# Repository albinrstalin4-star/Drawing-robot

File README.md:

# Drawing-robot
I want to create a drawing robot for my assignments. I think it will be helpful.This is my first project.This project is about building a simple drawing plotter robot that can automatically draw pictures and text on paper. It uses NEMA stepper motors to move a pen precisely along the X and Y directions.

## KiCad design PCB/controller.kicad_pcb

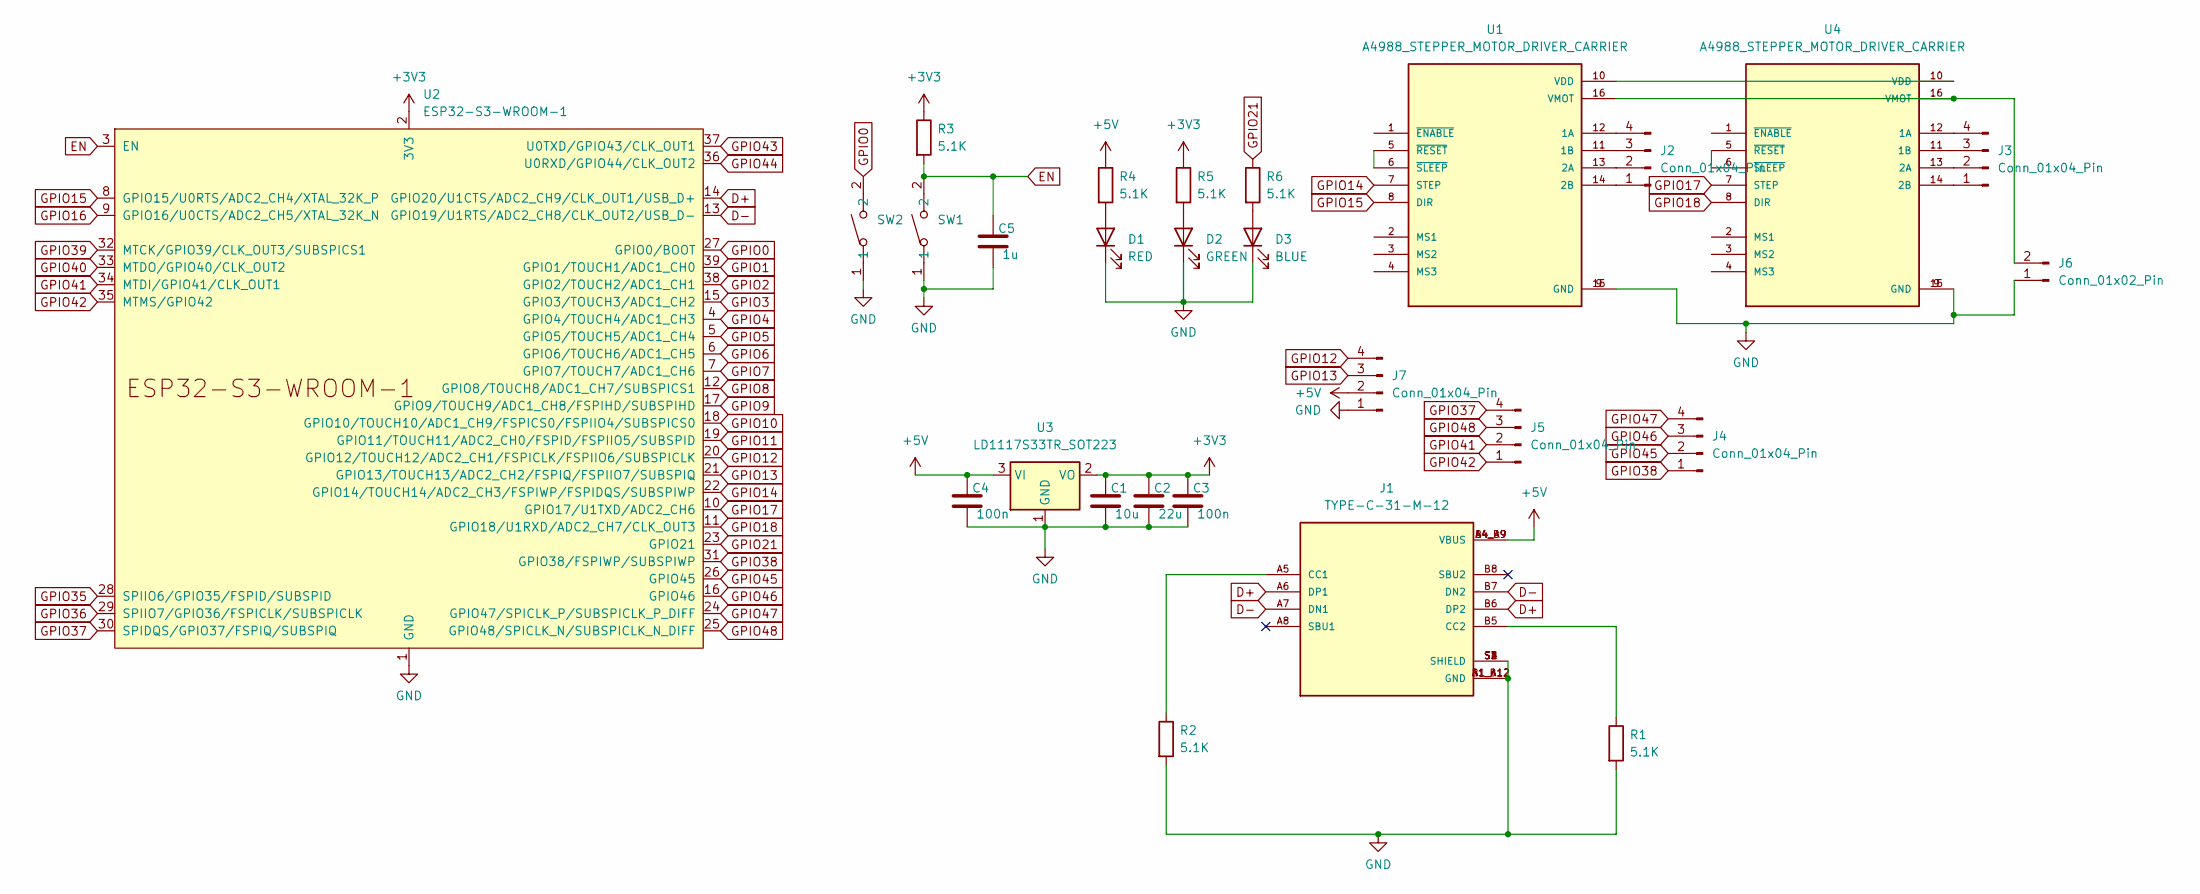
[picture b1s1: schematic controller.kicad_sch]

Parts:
C1: 10u; C_0603_1608Metric
C2: 22u; C_0603_1608Metric
C3, C4: 100n; C_0603_1608Metric
C5: 1u; C_0603_1608Metric
D1: RED; LED_0603_1608Metric
D2: GREEN; LED_0603_1608Metric
D3: BLUE; LED_0603_1608Metric
J1: TYPE-C-31-M-12; HRO_TYPE-C-31-M-12; PARTREV 2020.12.08
J2, J3, J4, J5, J7: Conn_01x04_Pin; PinSocket_1x04_P2.54mm_Vertical
J6: Conn_01x02_Pin; PinSocket_1x02_P2.54mm_Vertical
R1, R2, R3, R4, R5, R6: 5.1K; R_0603_1608Metric
SW1, SW2: TS-1088-AR02016; SW-SMD_L3.9-W3.0-P4.45; LCSC Part C720477
U1, U4: A4988_STEPPER_MOTOR_DRIVER_CARRIER; MODULE_A4988_STEPPER_MOTOR_DRIVER_CARRIER
U2: ESP32-S3-WROOM-1
U3: LD1117S33TR_SOT223; SOT-223-3_TabPin2

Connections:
+3V3: C1.1, C2.1, C3.1, R3.1, R5.1, U2.2 (3V3), U3.2 (VO)
+5V: C4.1, J1.A4_B9 (VBUS), J1.B4_A9 (VBUS), J7.2, R4.1, U3.3 (VI)
D+: J1.A6 (DP1), J1.B6 (DP2), U2.14 (GPIO20/U1CTS/ADC2_CH9/CLK_OUT1/USB_D+)
D-: J1.A7 (DN1), J1.B7 (DN2), U2.13 (GPIO19/U1RTS/ADC2_CH8/CLK_OUT2/USB_D-)
EN: C5.1, R3.2, SW1.2, U2.3 (EN)
GND: C1.2, C2.2, C3.2, C4.2, C5.2, D1.1 (K), D2.1 (K), D3.1 (K), J1.A1_B12 (GND), J1.B1_A12 (GND), J1.S1 (SHIELD), J1.S2 (SHIELD), J1.S3 (SHIELD), J1.S4 (SHIELD), J6.1, J7.1, R1.2, R2.2, SW1.1, SW2.1, U1.9 (GND), U1.15 (GND), U2.1 (GND), U2.40 (GND), U2.41 (GND), U3.1 (GND), U4.9 (GND), U4.15 (GND)
GPIO0: SW2.2, U2.27 (GPIO0/BOOT)
GPIO1: U2.39 (GPIO1/TOUCH1/ADC1_CH0)
GPIO2: U2.38 (GPIO2/TOUCH2/ADC1_CH1)
GPIO3: U2.15 (GPIO3/TOUCH3/ADC1_CH2)
GPIO4: U2.4 (GPIO4/TOUCH4/ADC1_CH3)
GPIO5: U2.5 (GPIO5/TOUCH5/ADC1_CH4)
GPIO6: U2.6 (GPIO6/TOUCH6/ADC1_CH5)
GPIO7: U2.7 (GPIO7/TOUCH7/ADC1_CH6)
GPIO8: U2.12 (GPIO8/TOUCH8/ADC1_CH7/SUBSPICS1)
GPIO9: U2.17 (GPIO9/TOUCH9/ADC1_CH8/FSPIHD/SUBSPIHD)
GPIO10: U2.18 (GPIO10/TOUCH10/ADC1_CH9/FSPICS0/FSPIIO4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)
GPIO11: U2.19 (GPIO11/TOUCH11/ADC2_CH0/FSPID/FSPIIO5/S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)
GPIO12: J7.4, U2.20 (GPIO12/TOUCH12/ADC2_CH1/FSPICLK/FSPIIO6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)
GPIO13: J7.3, U2.21 (GPIO13/TOUCH13/ADC2_CH2/FSPIQ/FSPIIO7/S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)
GPIO14: U1.7 (STEP), U2.22 (GPIO14/TOUCH14/ADC2_CH3/FSPIWP/FSPIDQS/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)
GPIO15: U1.8 (DIR), U2.8 (GPIO15/U0RTS/ADC2_CH4/XTAL_32K_P)
GPIO16: U2.9 (GPIO16/U0CTS/ADC2_CH5/XTAL_32K_N)
GPIO17: U2.10 (GPIO17/U1TXD/ADC2_CH6), U4.7 (STEP)
GPIO18: U2.11 (GPIO18/U1RXD/ADC2_CH7/CLK_OUT3), U4.8 (DIR)
GPIO21: R6.1, U2.23 (GPIO21)
GPIO35: U2.28 (SPIIO6/GPIO35/FSPID/SUBSPID)
GPIO36: U2.29 (SPIIO7/GPIO36/FSPICLK/SUBSPICLK)
GPIO37: J5.4, U2.30 (SPIDQS/GPIO37/FSPIQ/SUBSPIQ)
GPIO38: J4.1, U2.31 (GPIO38/FSPIWP/SUBSPIWP)
GPIO39: U2.32 (MTCK/GPIO39/CLK_OUT3/SUBSPICS1)
GPIO40: U2.33 (MTDO/GPIO40/CLK_OUT2)
GPIO41: J5.2, U2.34 (MTDI/GPIO41/CLK_OUT1)
GPIO42: J5.1, U2.35 (MTMS/GPIO42)
GPIO43: U2.37 (U0TXD/GPIO43/CLK_OUT1)
GPIO44: U2.36 (U0RXD/GPIO44/CLK_OUT2)
GPIO45: J4.2, U2.26 (GPIO45)
GPIO46: J4.3, U2.16 (GPIO46)
GPIO47: J4.4, U2.24 (GPIO47/SPICLK_P/SUBSPICLK_P_DIFF)
GPIO48: J5.3, U2.25 (GPIO48/SPICLK_N/SUBSPICLK_N_DIFF)
unnamed: D1.2 (A), R4.2
unnamed: D2.2 (A), R5.2
unnamed: D3.2 (A), R6.2
unnamed: J1.A5 (CC1), R2.1
unnamed: J1.B5 (CC2), R1.1
unnamed: J2.1, U1.14 (2B)
unnamed: J2.2, U1.13 (2A)
unnamed: J2.3, U1.11 (1B)
unnamed: J2.4, U1.12 (1A)
unnamed: J3.1, U4.14 (2B)
unnamed: J3.2, U4.13 (2A)
unnamed: J3.3, U4.11 (1B)
unnamed: J3.4, U4.12 (1A)
unnamed: J6.2, U1.16 (VMOT), U4.16 (VMOT)
unnamed: U1.10 (VDD), U4.10 (VDD)
unnamed: U1.5 (~RESET), U1.6 (~SLEEP)
unnamed: U4.5 (~RESET), U4.6 (~SLEEP)

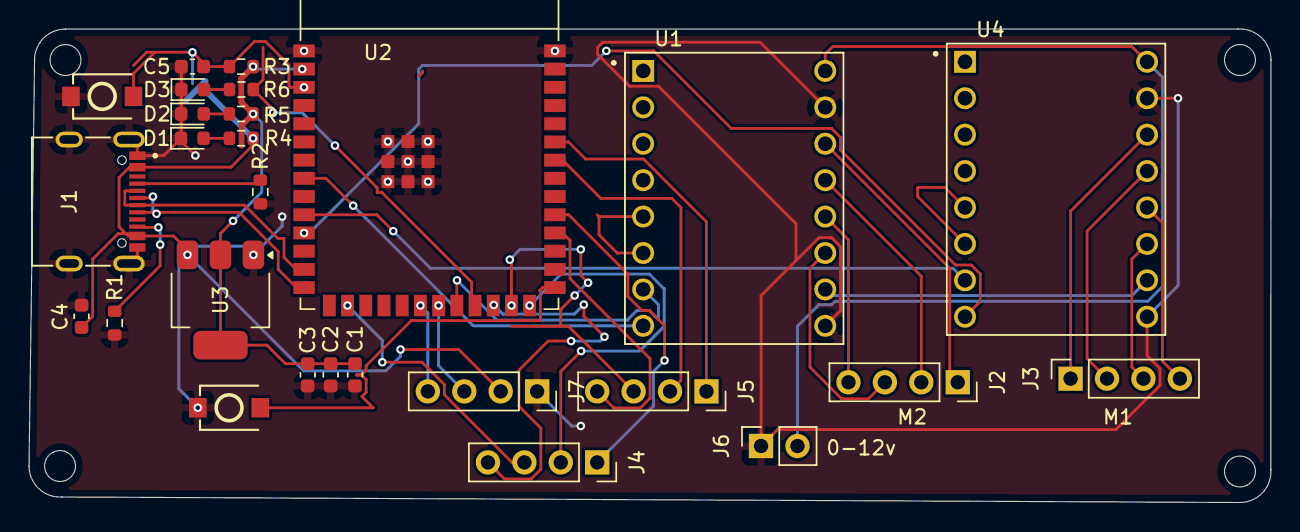
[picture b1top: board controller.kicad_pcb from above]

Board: 2 copper layers, 86.6 x 33.0 mm, 27 parts (0 on the bottom side), 39 nets.

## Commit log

2026-01-21 Create new folder
2026-01-21 Rename .gitkeep to PCB
2026-01-21 Rename PCB/PCB to PCB.gitkeep
2026-01-21 Rename PCB.GITKEEP to PCB/.gitkeep
2026-01-24 Create CAD
2026-01-24 Rename CAD/ draw.jpeg
2026-01-24 Rename WhatsApp Image 2026-01-21 at 7.20.30 PM.jpeg to PCB.jpeg
2026-01-24 Delete BOM.csv
    details of materials for making drawing robot
2026-01-24 Rename PCB.jpeg to PCB.jpeg
    Picture of PCB
2026-01-24 Rename PCBB.jpeg to PCB.jpeg
    picture of PCB
2026-01-24 Fix formatting and add entries in BOM file
    Updated BOM file to correct formatting and add missing entries.
2026-01-24 Fix BOM CSV formatting and currency symbols
2026-01-24 Fix BOM file formatting and totals
    Updated BOM file with corrected subtotal and total values.
2026-01-24 Fix formatting and update entries in BOM file
    Updated BOM file to correct formatting and add missing entries.
2026-01-24 Fix BOM formatting and add product entries
    Updated BOM file to correct formatting and add products.
2026-01-24 Modify BOM with new product entries and prices
    Updated product list and corrected pricing for BOM.
2026-01-26 Rename 2026-01-16 at 9.46.21 PM.jpeg to CAD.jpeg
2026-01-28 Add image upload link to README
    Added a new image upload link to the README.
